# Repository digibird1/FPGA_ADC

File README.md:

FPGA_ADC
========

Interface the AD9057 with a Cyclone III FPGA including USB 2.0 communication FTDI FT232.

Detailed description:
http://digibird1.wordpress.com/adc-readout-and-usb2-0-data-transfer-with-an-fpga/

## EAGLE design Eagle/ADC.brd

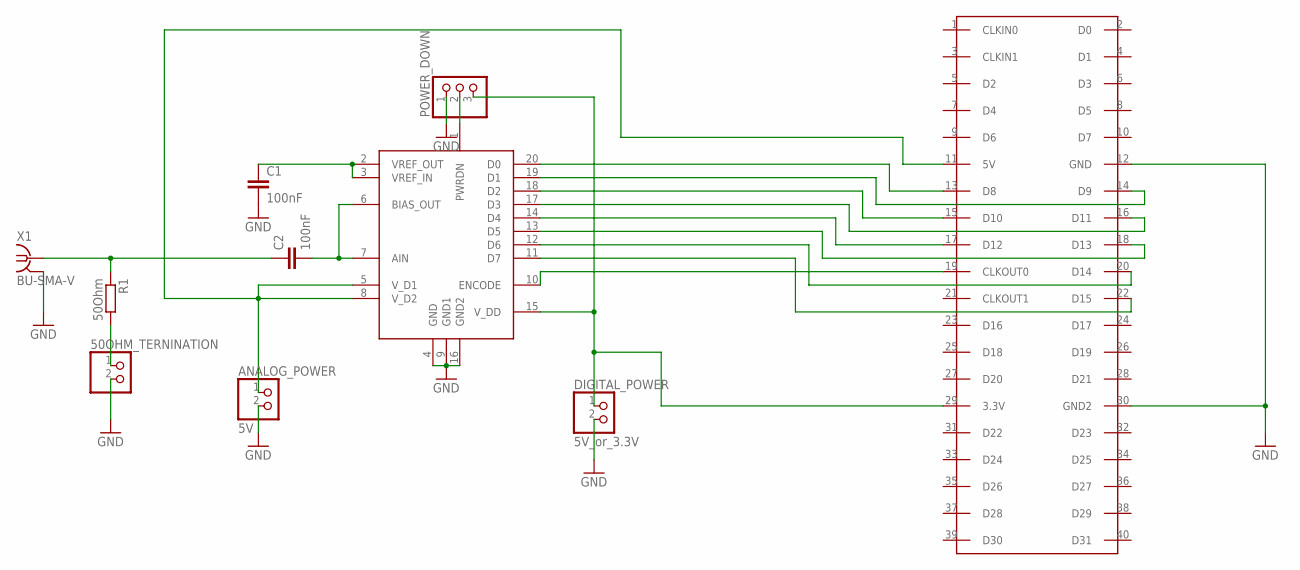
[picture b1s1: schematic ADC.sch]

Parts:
50OHM_TERNINATION: PINHD-1X2; 1X02
ANALOG_POWER: 5V; 1X02
C1, C2: 100nF; C2.5-5
DIGITAL_POWER: 5V_or_3.3V; 1X02
POWER_DOWN: PINHD-1X3; 1X03
R1: 50Ohm; 0207/10
U$1: AD9057; SSOP20
U$2: FPGA_GPIO_DE0; 2X20
X1: BU-SMA-V

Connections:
GND: 50OHM_TERNINATION.2, ANALOG_POWER.2, C1.2, DIGITAL_POWER.2, POWER_DOWN.1, U$1.4 (GND), U$1.9 (GND1), U$1.16 (GND2), U$2.12 (GND), U$2.30 (GND2), X1.2, X1.3 (2), X1.4 (2), X1.5 (2)
unnamed: C2.2, U$1.6 (BIAS_OUT), U$1.7 (AIN)
unnamed: C1.1, U$1.2 (VREF_OUT), U$1.3 (VREF_IN)
unnamed: DIGITAL_POWER.1, POWER_DOWN.3, U$1.15 (V_DD), U$2.29 (3.3V)
unnamed: C2.1, R1.1, X1.1
unnamed: POWER_DOWN.2, U$1.1 (PWRDN)
unnamed: U$1.20 (D0), U$2.13 (D8)
unnamed: U$1.19 (D1), U$2.14 (D9)
unnamed: U$1.18 (D2), U$2.15 (D10)
unnamed: U$1.17 (D3), U$2.16 (D11)
unnamed: U$1.14 (D4), U$2.17 (D12)
unnamed: U$1.13 (D5), U$2.18 (D13)
unnamed: U$1.12 (D6), U$2.20 (D14)
unnamed: U$1.11 (D7), U$2.22 (D15)
unnamed: U$1.10 (ENCODE), U$2.19 (CLKOUT0)
unnamed: ANALOG_POWER.1, U$1.5 (V_D1), U$1.8 (V_D2), U$2.11 (5V)
unnamed: 50OHM_TERNINATION.1, R1.2

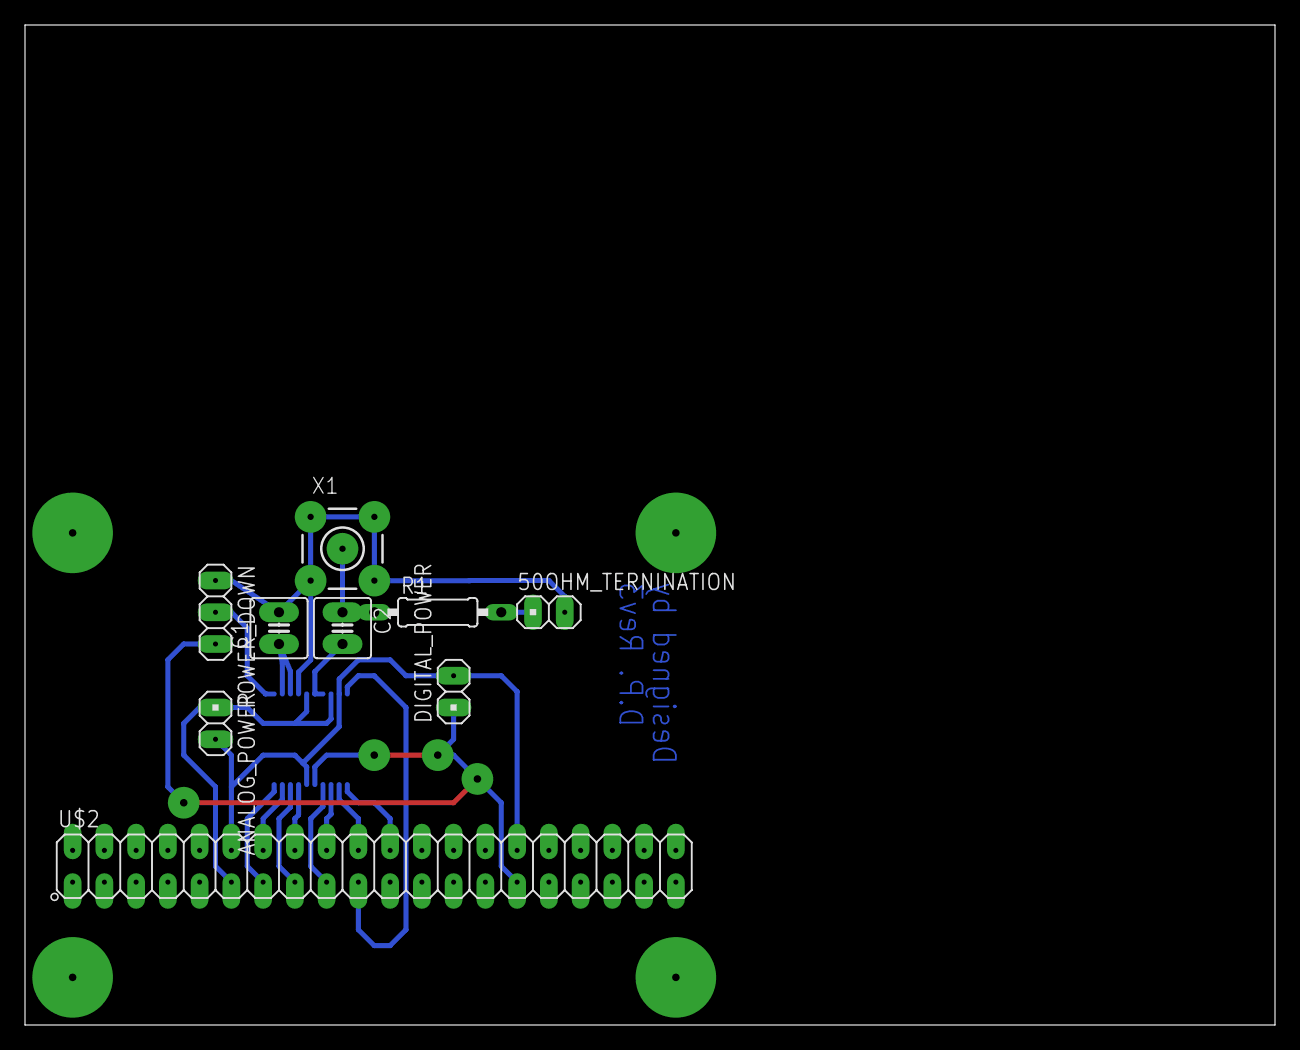
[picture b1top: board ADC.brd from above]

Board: 2 copper layers, 100.0 x 80.0 mm, 10 parts (1 on the bottom side), 17 nets.

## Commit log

2014-08-04 First Check In
2014-08-07 Added more files
2014-08-07 Changed Readme
